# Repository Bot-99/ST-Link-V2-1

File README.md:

# ST-Link-V2-1

typec
stlink + ttl

cfg: stlink-v2.cfg / stlink-v2_1.cfg

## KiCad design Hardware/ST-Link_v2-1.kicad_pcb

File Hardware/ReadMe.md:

# ST- Link V2-1

## Target:

1. 0402
2. Single side Component
3. Type C

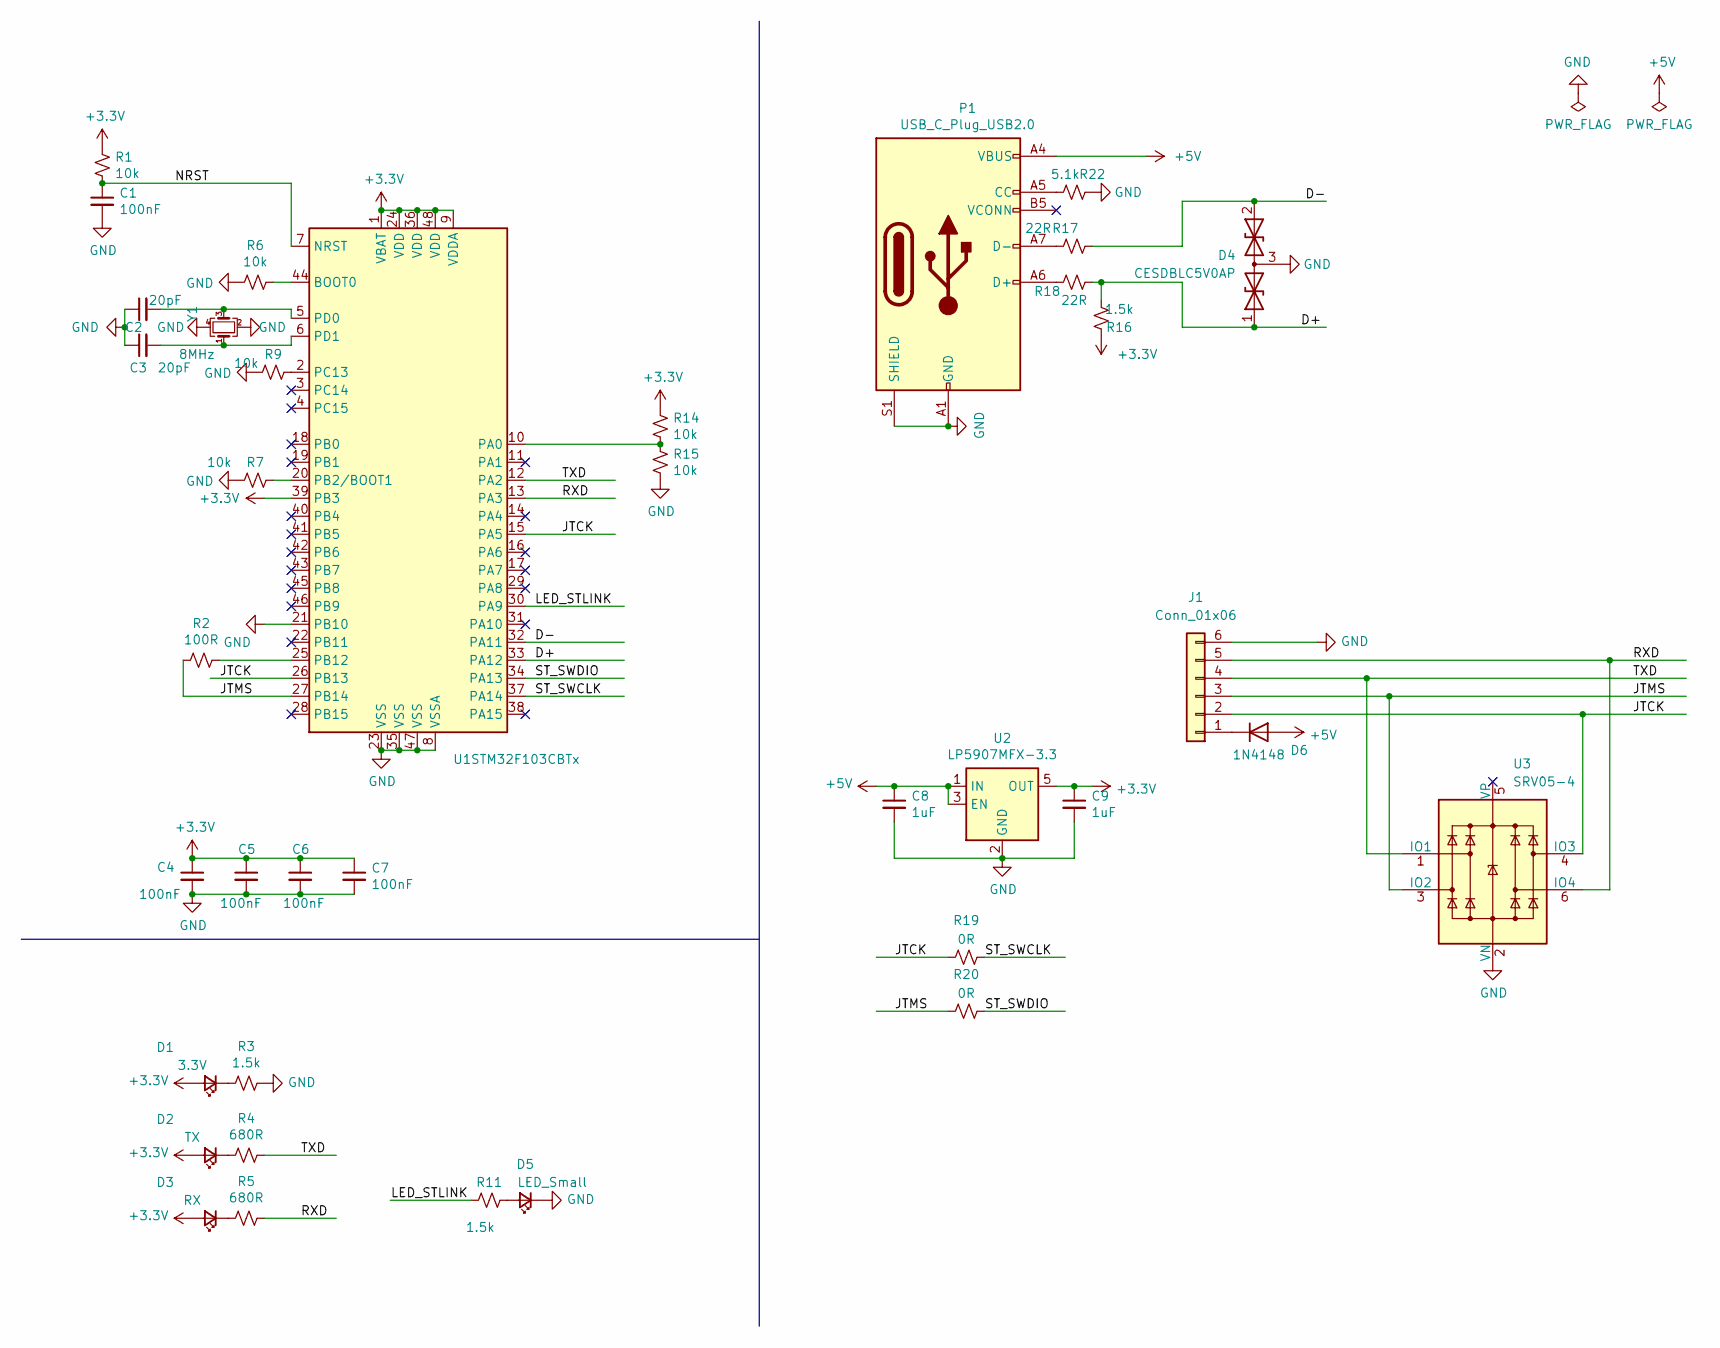
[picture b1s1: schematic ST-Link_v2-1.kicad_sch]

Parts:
C1, C4, C5, C6, C7: 100nF; C_0603_1608Metric
C2, C3: 20pF; C_0603_1608Metric
C8, C9: 1uF; C_0603_1608Metric
D1: 3.3V; LED_0603_1608Metric
D2: TX; LED_0603_1608Metric
D3: RX; LED_0603_1608Metric
D4: CESDBLC5V0AP; SOT-23
D5: LED_Small; LED_0603_1608Metric
D6: 1N4148; SOD-8OC
J1: Conn_01x06; JST_GH_SM06B-GHS-TB_1x06-1MP_P1.25mm_Horizontal
P1: USB_C_Plug_USB2.0; USB_C_MALE
R1, R6, R7, R9, R14, R15: 10k; R_0603_1608Metric
R2: 100R; R_0603_1608Metric
R3, R11, R16: 1.5k; R_0603_1608Metric
R4, R5: 680R; R_0603_1608Metric
R17, R18: 22R; R_0603_1608Metric
R19, R20: 0R; R_0603_1608Metric
R22: 5.1k; R_0603_1608Metric
U1: STM32F103CBTx; LQFP-48_7x7mm_P0.5mm
U2: LP5907MFX-3.3; SOT-23-5
U3: SRV05-4; SOT-23-6
Y1: 8MHz; Crystal_SMD_3225-4Pin_3.2x2.5mm

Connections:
+3V3: C4.1, C5.1, C6.1, C7.1, C9.1, D1.2 (A), D2.2 (A), D3.2 (A), R1.2, R14.2, R16.1, U1.1 (VBAT), U1.9 (VDDA), U1.24 (VDD), U1.36 (VDD), U1.39 (PB3), U1.48 (VDD), U2.5 (OUT)
+5V: C8.1, D6.2 (A), P1.A4 (VBUS), P1.A9 (VBUS), P1.B4 (VBUS), P1.B9 (VBUS), U2.1 (IN), U2.3 (EN)
/D+: D4.1 (A1), R16.2, R18.1, U1.33 (PA12)
/D-: D4.2 (A2), R17.1, U1.32 (PA11)
/JTCK: J1.2, R19.2, U1.15 (PA5), U1.26 (PB13), U3.4 (IO3)
/JTMS: J1.3, R2.2, R20.2, U1.27 (PB14), U3.3 (IO2)
/LED_STLINK: R11.2, U1.30 (PA9)
/NRST: C1.1, R1.1, U1.7 (NRST)
/RXD: J1.5, R5.1, U1.13 (PA3), U3.6 (IO4)
/ST_SWCLK: R19.1, U1.37 (PA14)
/ST_SWDIO: R20.1, U1.34 (PA13)
/TXD: J1.4, R4.1, U1.12 (PA2), U3.1 (IO1)
GND: C1.2, C2.1, C3.1, C4.2, C5.2, C6.2, C7.2, C8.2, C9.2, D4.3 (common), D5.1 (K), J1.6, P1.A1 (GND), P1.A12 (GND), P1.B1 (GND), P1.B12 (GND), P1.S1 (SHIELD), R3.1, R6.2, R7.2, R9.2, R15.1, R22.2, U1.8 (VSSA), U1.21 (PB10), U1.23 (VSS), U1.35 (VSS), U1.47 (VSS), U2.2 (GND), U3.2 (VN), Y1.2, Y1.4
unnamed: D1.1 (K), R3.2
unnamed: D2.1 (K), R4.2
unnamed: D3.1 (K), R5.2
unnamed: D5.2 (A), R11.1
unnamed: D6.1 (K), J1.1
unnamed: P1.A5 (CC), R22.1
unnamed: P1.A6 (D+), R18.2
unnamed: P1.A7 (D-), R17.2
unnamed: R2.1, U1.25 (PB12)
unnamed: R6.1, U1.44 (BOOT0)
unnamed: R7.1, U1.20 (PB2/BOOT1)
unnamed: R9.1, U1.2 (PC13)
unnamed: R14.1, R15.2, U1.10 (PA0)
unnamed: C2.2, U1.5 (PD0), Y1.3
unnamed: C3.2, U1.6 (PD1), Y1.1

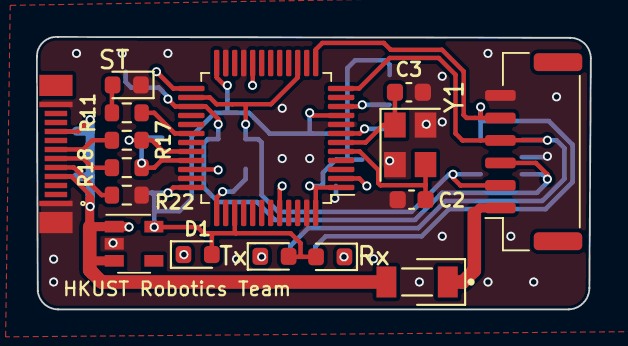
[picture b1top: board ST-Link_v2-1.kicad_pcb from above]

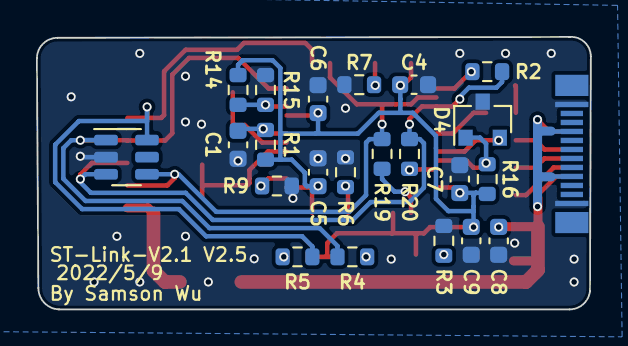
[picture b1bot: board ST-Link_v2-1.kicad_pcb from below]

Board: 2 copper layers, 30.8 x 15.1 mm, 38 parts (22 on the bottom side), 28 nets.

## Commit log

2021-11-13 hardwware
2021-11-14 source
2021-11-16 16-11-2021
2021-11-17 18-11-2021
2021-11-19 20-11-2021
2021-11-21 21-11-2021
2021-11-23 1.2.2
2021-12-01 v2 2/12/2021
2021-12-03 find bug in sch
2021-12-04 5/12/2021
2021-12-10 V2.1 11/12/2021
2021-12-27 v2.2
2022-01-23 v2.3
2022-01-24 readme
2022-03-02 Done
2022-04-11 2.4 add esd protection
2022-04-11 2.4 desgin rule check
2022-05-08 v2.5
